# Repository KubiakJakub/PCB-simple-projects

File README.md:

# PCB simple projects
 Repo made for learning purpose only

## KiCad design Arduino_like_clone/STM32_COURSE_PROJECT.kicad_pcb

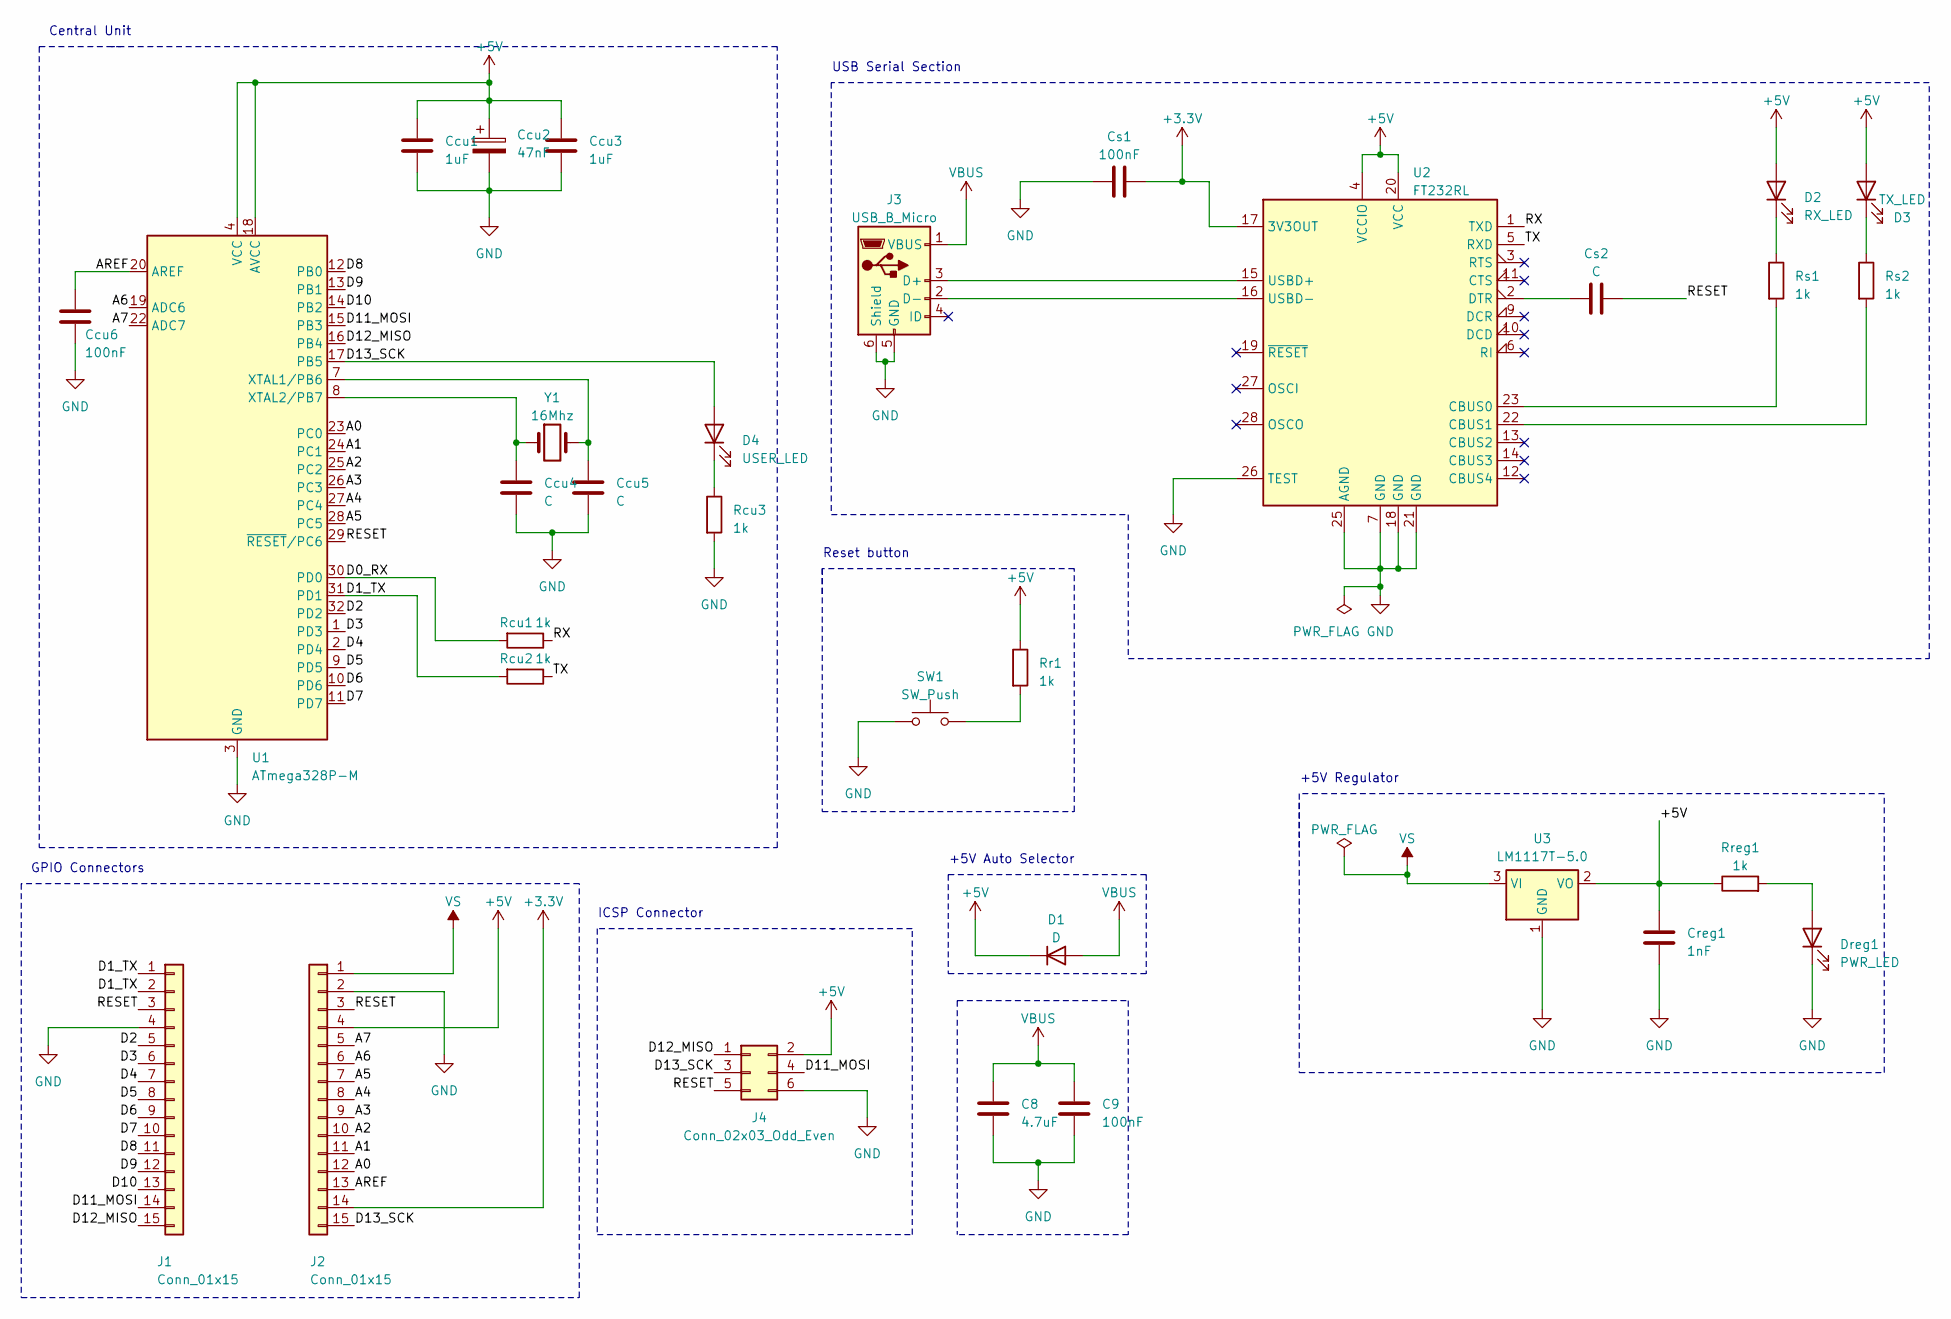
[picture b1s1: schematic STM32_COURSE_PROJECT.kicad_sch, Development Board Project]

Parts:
C8: 4.7uF; C_1206_3216Metric_Pad1.33x1.80mm_HandSolder
C9: 100nF; C_0805_2012Metric_Pad1.18x1.45mm_HandSolder
Ccu1, Ccu3: 1uF; C_0805_2012Metric_Pad1.18x1.45mm_HandSolder
Ccu2: 47nF; C_1206_3216Metric_Pad1.33x1.80mm_HandSolder
Ccu4, Ccu5: C; C_0805_2012Metric_Pad1.18x1.45mm_HandSolder
Ccu6: 100nF; C_0805_2012Metric_Pad1.18x1.45mm_HandSolder
Creg1: 1nF; C_0805_2012Metric_Pad1.18x1.45mm_HandSolder
Cs1: 100nF; C_0805_2012Metric_Pad1.18x1.45mm_HandSolder
Cs2: C; C_0805_2012Metric_Pad1.18x1.45mm_HandSolder
D1: D; D_SOD-123
D2: RX_LED; LED_0603_1608Metric_Pad1.05x0.95mm_HandSolder
D3: TX_LED; LED_0603_1608Metric_Pad1.05x0.95mm_HandSolder
D4: USER_LED; LED_0603_1608Metric_Pad1.05x0.95mm_HandSolder
Dreg1: PWR_LED; LED_0603_1608Metric_Pad1.05x0.95mm_HandSolder
J1, J2: Conn_01x15; PinHeader_1x15_P2.54mm_Vertical
J3: USB_B_Micro; USB_Mini-B_Lumberg_2486_01_Horizontal
J4: Conn_02x03_Odd_Even; PinHeader_2x03_P2.54mm_Vertical
Rcu1, Rcu2, Rcu3: 1k; R_0805_2012Metric_Pad1.20x1.40mm_HandSolder
Rr1: 1k; R_0805_2012Metric_Pad1.20x1.40mm_HandSolder
Rreg1: 1k; R_0805_2012Metric_Pad1.20x1.40mm_HandSolder
Rs1, Rs2: 1k; R_0805_2012Metric_Pad1.20x1.40mm_HandSolder
SW1: SW_Push; SW_Push_1P1T_NO_6x6mm_H9.5mm
U1: ATmega328P-M; QFN-32-1EP_5x5mm_P0.5mm_EP3.1x3.1mm
U2: FT232RL; SSOP-28_5.3x10.2mm_P0.65mm
U3: LM1117T-5.0; TO-220-3_Horizontal_TabDown
Y1: 16Mhz; Crystal_SMD_3225-4Pin_3.2x2.5mm_HandSoldering

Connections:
+3.3V: Cs1.2, J2.14, U2.17 (3V3OUT)
+5V: Ccu1.1, Ccu2.1, Ccu3.1, Creg1.1, D1.1 (K), D2.2 (A), D3.2 (A), J2.4, J4.2, Rr1.1, Rreg1.1, U1.4 (VCC), U1.6 (VCC), U1.18 (AVCC), U2.4 (VCCIO), U2.20 (VCC), U3.2 (VO)
/A0: J2.12, U1.23 (PC0)
/A1: J2.11, U1.24 (PC1)
/A2: J2.10, U1.25 (PC2)
/A3: J2.9, U1.26 (PC3)
/A4: J2.8, U1.27 (PC4)
/A5: J2.7, U1.28 (PC5)
/A6: J2.6, U1.19 (ADC6)
/A7: J2.5, U1.22 (ADC7)
/AREF: Ccu6.1, J2.13, U1.20 (AREF)
/D0_RX: Rcu1.2, U1.30 (PD0)
/D1_TX: J1.1, J1.2, Rcu2.2, U1.31 (PD1)
/D2: J1.5, U1.32 (PD2)
/D3: J1.6, U1.1 (PD3)
/D4: J1.7, U1.2 (PD4)
/D5: J1.8, U1.9 (PD5)
/D6: J1.9, U1.10 (PD6)
/D7: J1.10, U1.11 (PD7)
/D8: J1.11, U1.12 (PB0)
/D9: J1.12, U1.13 (PB1)
/D10: J1.13, U1.14 (PB2)
/D11_MOSI: J1.14, J4.4, U1.15 (PB3)
/D12_MISO: J1.15, J4.1, U1.16 (PB4)
/D13_SCK: D4.2 (A), J2.15, J4.3, U1.17 (PB5)
/RESET: Cs2.2, J1.3, J2.3, J4.5, U1.29 (~RESET/PC6)
/RX: Rcu1.1, U2.1 (TXD)
/TX: Rcu2.1, U2.5 (RXD)
GND: C8.2, C9.2, Ccu1.2, Ccu2.2, Ccu3.2, Ccu4.2, Ccu5.2, Ccu6.2, Creg1.2, Cs1.1, Dreg1.1 (K), J1.4, J2.2, J3.5 (GND), J3.6 (Shield), J4.6, Rcu3.2, SW1.1, U1.3 (GND), U1.5 (GND), U1.21 (GND), U1.33 (GND), U2.7 (GND), U2.18 (GND), U2.21 (GND), U2.25 (AGND), U2.26 (TEST), U3.1 (GND)
unnamed: D2.1 (K), Rs1.1
unnamed: D3.1 (K), Rs2.1
unnamed: D4.1 (K), Rcu3.1
unnamed: Dreg1.2 (A), Rreg1.2
unnamed: J3.3 (D+), U2.15 (USBD+)
unnamed: J3.2 (D-), U2.16 (USBD-)
unnamed: Rr1.2, SW1.2
unnamed: Ccu5.1, U1.7 (XTAL1/PB6), Y1.2
unnamed: Ccu4.1, U1.8 (XTAL2/PB7), Y1.1
unnamed: Rs1.2, U2.23 (CBUS0)
unnamed: Rs2.2, U2.22 (CBUS1)
unnamed: Cs2.1, U2.2 (DTR)
VBUS: C8.1, C9.1, D1.2 (A), J3.1 (VBUS)
VS: J2.1, U3.3 (VI)

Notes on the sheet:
+5V Auto Selector
GPIO Connectors
Central Unit
USB Serial Section
+5V Regulator
Reset button
ICSP Connector

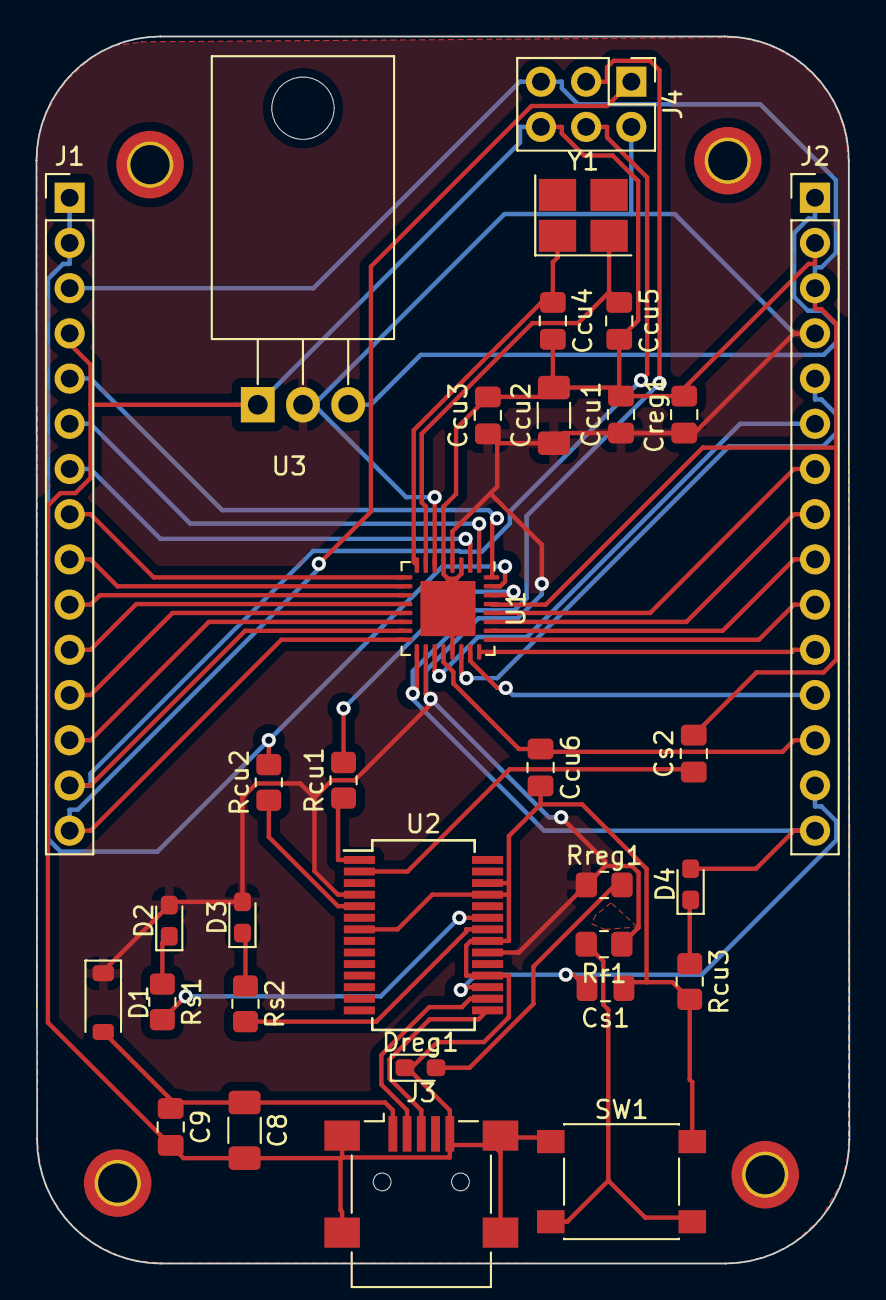
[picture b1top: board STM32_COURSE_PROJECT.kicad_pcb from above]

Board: 2 copper layers, 45.7 x 68.9 mm, 32 parts (0 on the bottom side), 43 nets.

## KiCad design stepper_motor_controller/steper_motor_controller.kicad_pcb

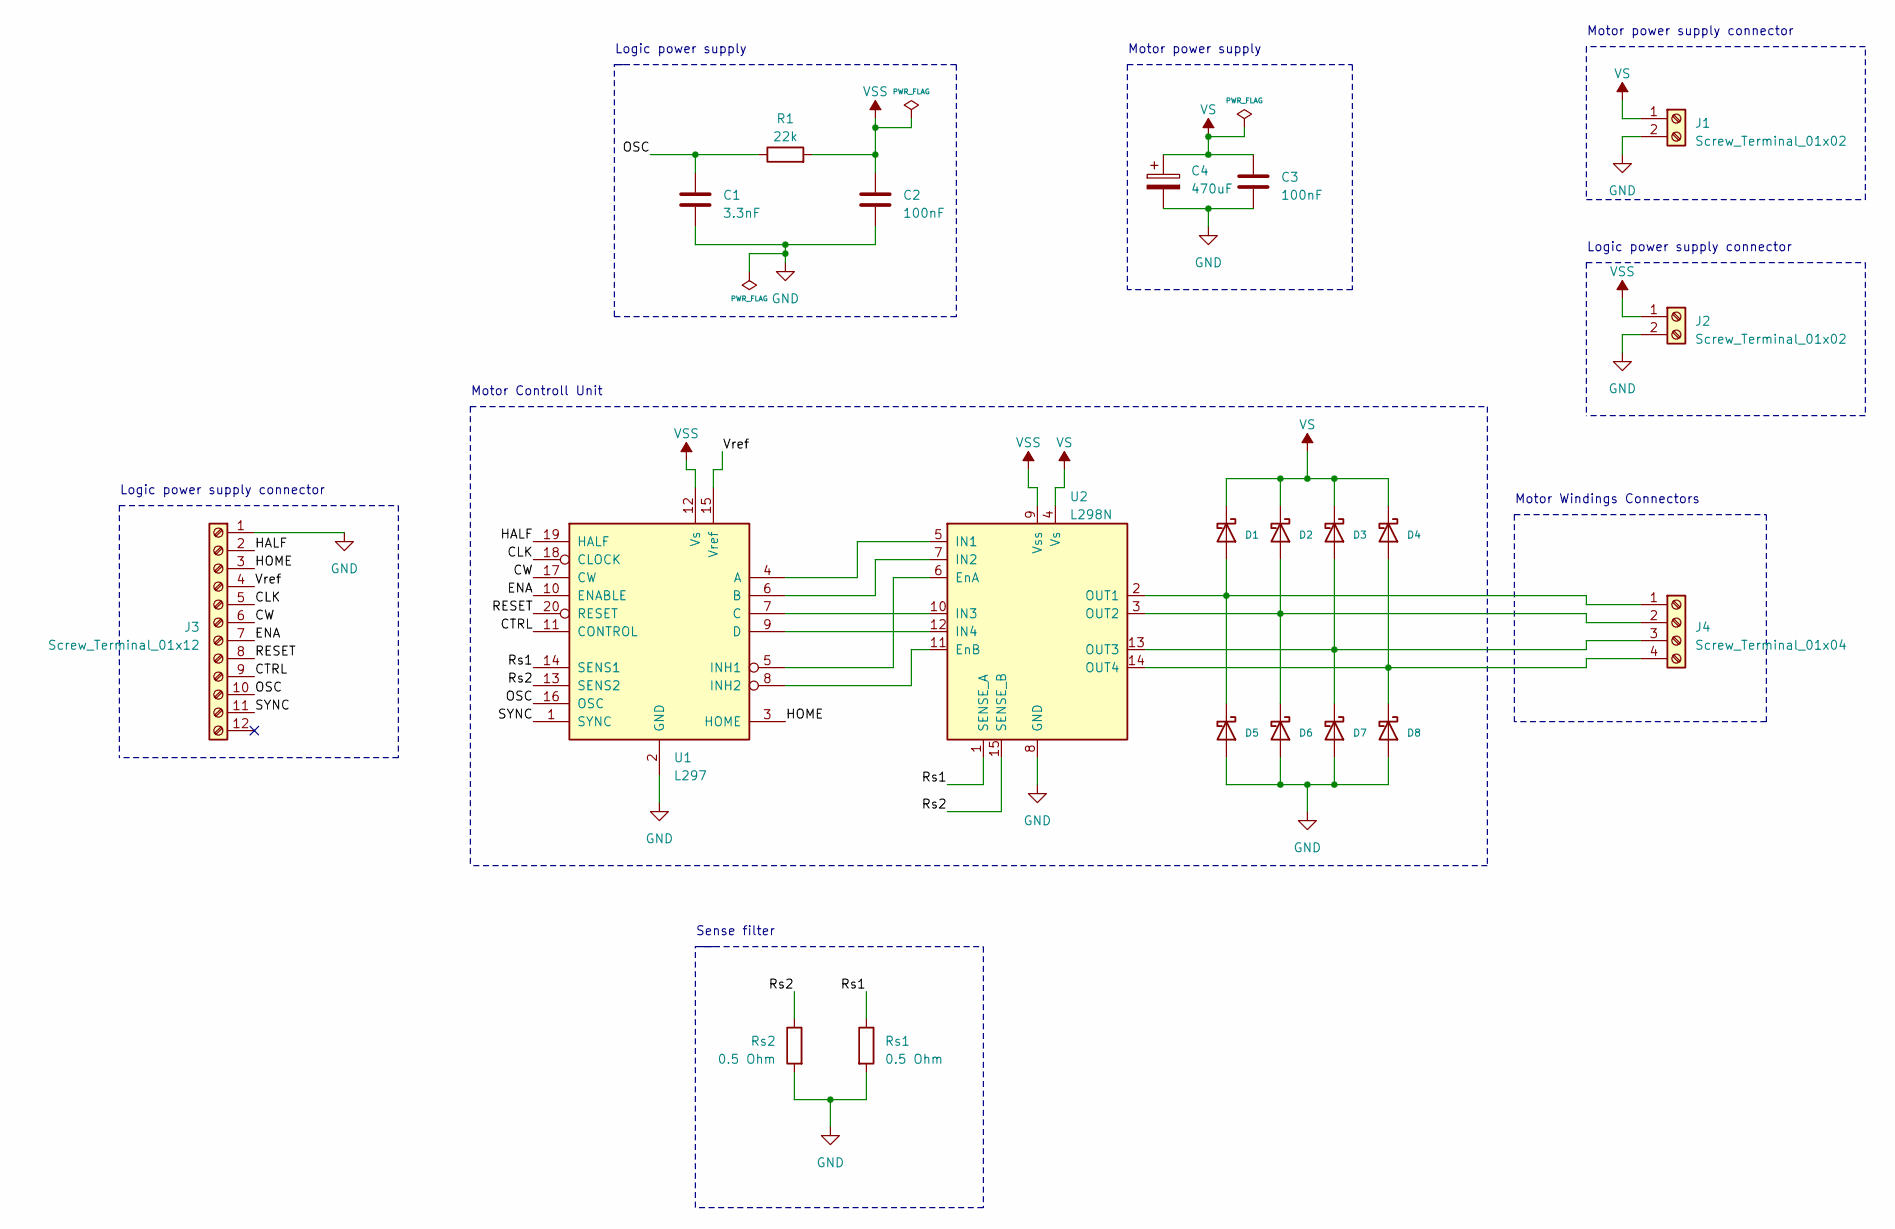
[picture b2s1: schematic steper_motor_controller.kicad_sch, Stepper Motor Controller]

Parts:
C1: 3.3nF; C_Rect_L10.0mm_W3.0mm_P7.50mm_FKS3_FKP3
C2, C3: 100nF; C_Rect_L7.5mm_W6.5mm_P5.00mm
C4: 470uF; CP_Radial_D13.0mm_P5.00mm
D1, D2, D3, D4, D5, D6, D7, D8: D_Schottky; D_DO-27_P15.24mm_Horizontal
J1, J2: Screw_Terminal_01x02; TerminalBlock_Phoenix_MKDS-1,5-2-5.08_1x02_P5.08mm_Horizont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
J3: Screw_Terminal_01x12; TerminalBlock_Phoenix_MKDS-3-12-5.08_1x12_P5.08mm_Horizontal
J4: Screw_Terminal_01x04; TerminalBlock_Phoenix_MKDS-1,5-4-5.08_1x04_P5.08mm_Horizont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
R1: 22k; R_Axial_DIN0922_L20.0mm_D9.0mm_P25.40mm_Horizontal
Rs1, Rs2: 0.5 Ohm; R_Axial_DIN0414_L11.9mm_D4.5mm_P15.24mm_Horizontal
U1: L297; DIP-20_W7.62mm
U2: L298N; TO-220-15_P2.54x2.54mm_StaggerOdd_Lead4.58mm_Vertical

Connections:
/CLK: J3.5, U1.18 (CLOCK)
/CTRL: J3.9, U1.11 (CONTROL)
/CW: J3.6, U1.17 (CW)
/ENA: J3.7, U1.10 (ENABLE)
/HALF: J3.2, U1.19 (HALF)
/HOME: J3.3, U1.3 (HOME)
/OSC: C1.1, J3.10, R1.1, U1.16 (OSC)
/RESET: J3.8, U1.20 (RESET)
/Rs1: Rs1.1, U1.14 (SENS1), U2.1 (SENSE_A)
/Rs2: Rs2.1, U1.13 (SENS2), U2.15 (SENSE_B)
/SYNC: J3.11, U1.1 (SYNC)
/Vref: J3.4, U1.15 (Vref)
GND: C1.2, C2.2, C3.2, C4.2, D5.2 (A), D6.2 (A), D7.2 (A), D8.2 (A), J1.2, J2.2, J3.1, Rs1.2, Rs2.2, U1.2 (GND), U2.8 (GND)
unnamed: D1.2 (A), D5.1 (K), J4.1, U2.2 (OUT1)
unnamed: D2.2 (A), D6.1 (K), J4.2, U2.3 (OUT2)
unnamed: D3.2 (A), D7.1 (K), J4.3, U2.13 (OUT3)
unnamed: D4.2 (A), D8.1 (K), J4.4, U2.14 (OUT4)
unnamed: U1.4 (A), U2.5 (IN1)
unnamed: U1.6 (B), U2.7 (IN2)
unnamed: U1.7 (C), U2.10 (IN3)
unnamed: U1.9 (D), U2.12 (IN4)
unnamed: U1.5 (INH1), U2.6 (EnA)
unnamed: U1.8 (INH2), U2.11 (EnB)
VS: C3.1, C4.1, D1.1 (K), D2.1 (K), D3.1 (K), D4.1 (K), J1.1, U2.4 (Vs)
VSS: C2.1, J2.1, R1.2, U1.12 (Vs), U2.9 (Vss)

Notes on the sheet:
Sense filter
Motor power supply connector
Motor power supply
Logic power supply
Logic power supply connector
Motor Windings Connectors
Motor Controll Unit

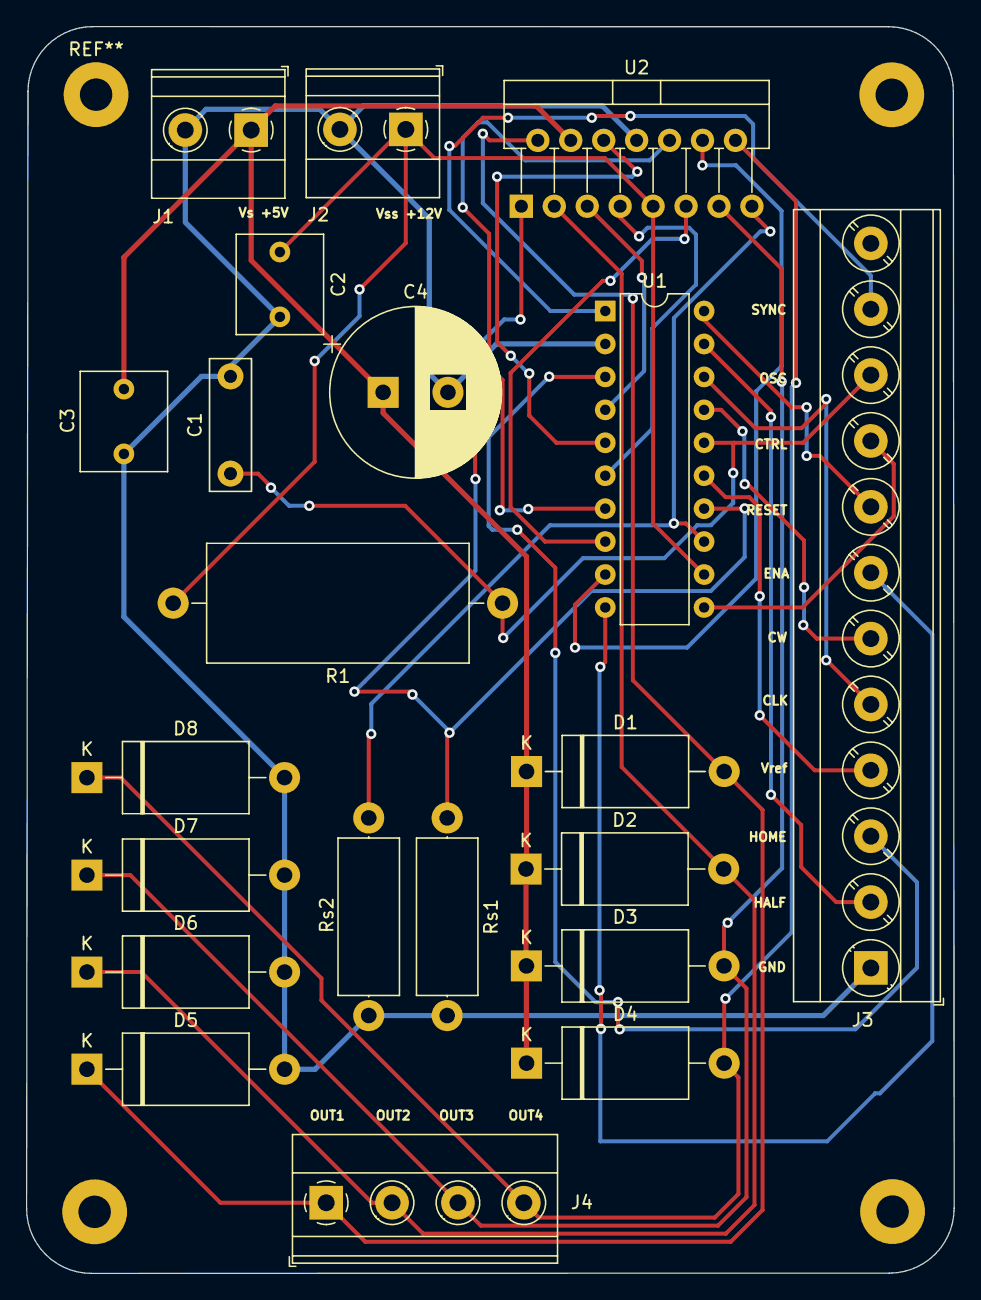
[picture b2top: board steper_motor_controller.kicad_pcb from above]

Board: 2 copper layers, 71.5 x 96.1 mm, 21 parts (0 on the bottom side), 25 nets.

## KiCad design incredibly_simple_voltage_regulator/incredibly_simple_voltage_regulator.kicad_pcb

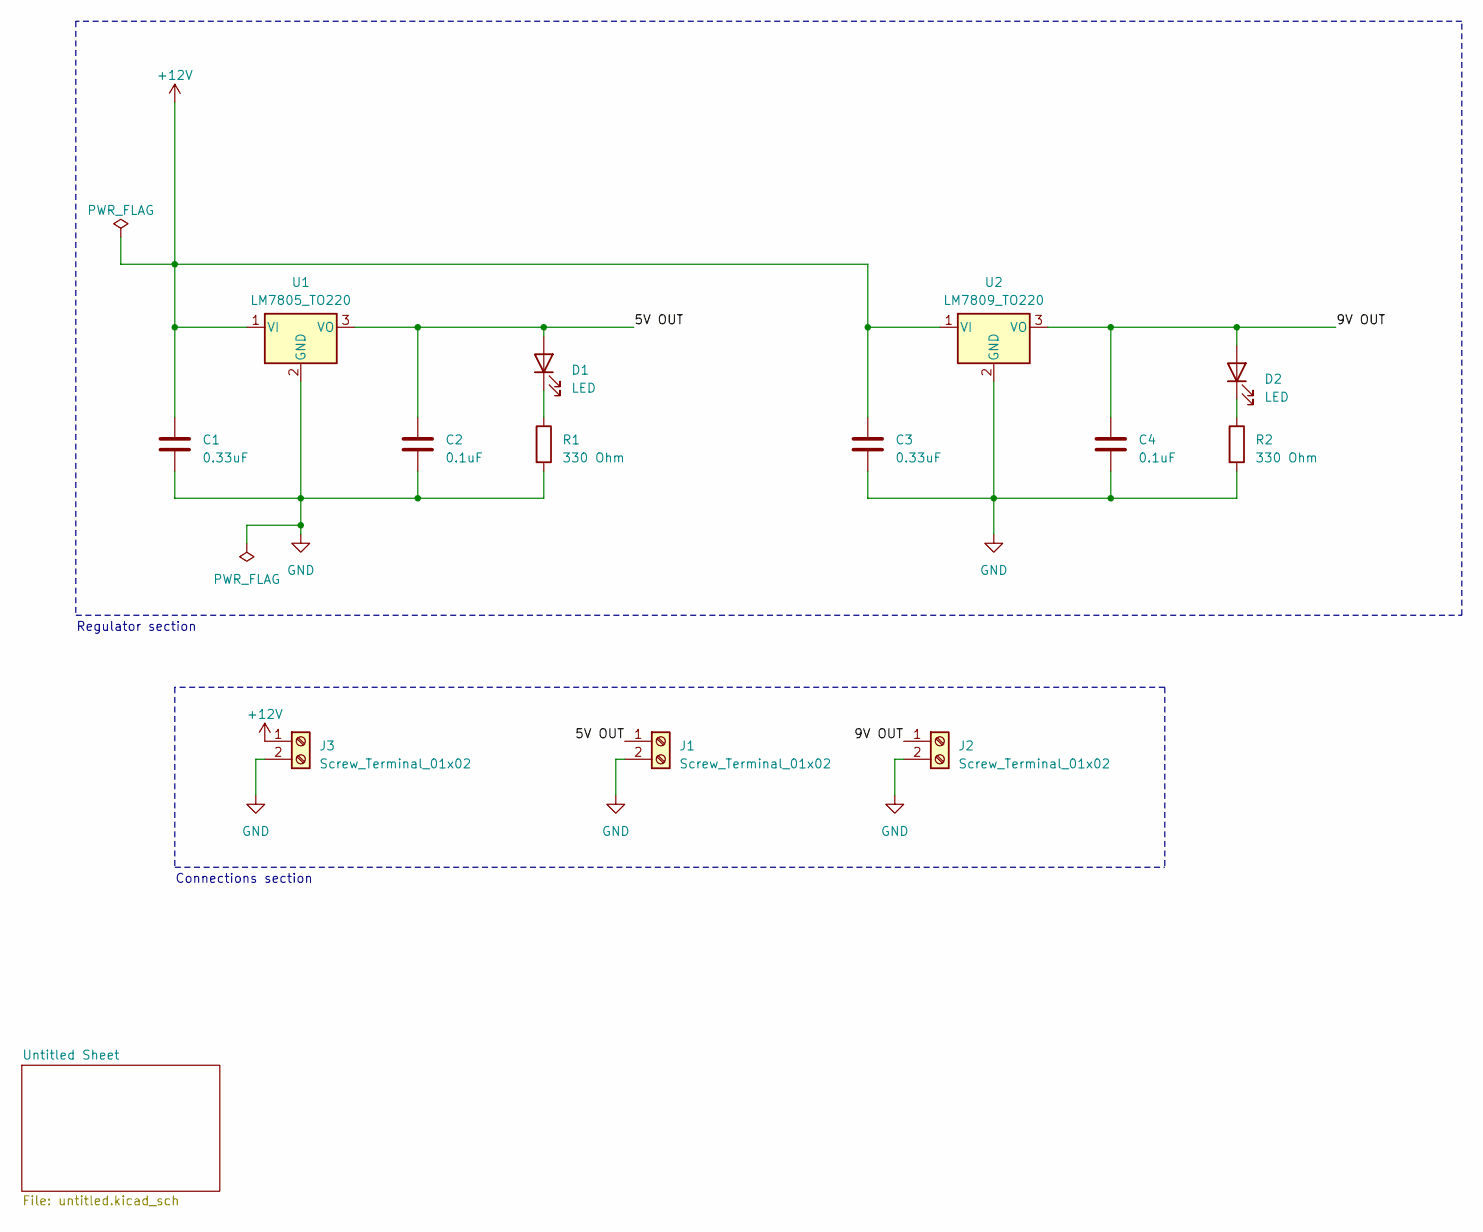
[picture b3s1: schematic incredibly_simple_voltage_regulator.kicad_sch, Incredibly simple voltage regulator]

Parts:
C1, C3: 0.33uF; C_Disc_D4.7mm_W2.5mm_P5.00mm
C2, C4: 0.1uF; C_Disc_D4.7mm_W2.5mm_P5.00mm
D1, D2: LED; LED_D4.0mm
J1, J2, J3: Screw_Terminal_01x02; TerminalBlock_Phoenix_MKDS-1,5-2_1x02_P5.00mm_Horizontal
R1, R2: 330 Ohm; R_Axial_DIN0207_L6.3mm_D2.5mm_P7.62mm_Horizontal
U1: LM7805_TO220; TO-220-3_Vertical
U2: LM7809_TO220; TO-220-3_Vertical

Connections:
+12V: C1.1, C3.1, J3.1, U1.1 (VI), U2.1 (VI)
/5V OUT: C2.1, D1.2 (A), J1.1, U1.3 (VO)
/9V OUT: C4.1, D2.2 (A), J2.1, U2.3 (VO)
GND: C1.2, C2.2, C3.2, C4.2, J1.2, J2.2, J3.2, R1.2, R2.2, U1.2 (GND), U2.2 (GND)
unnamed: D1.1 (K), R1.1
unnamed: D2.1 (K), R2.1

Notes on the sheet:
Connections section
Regulator section

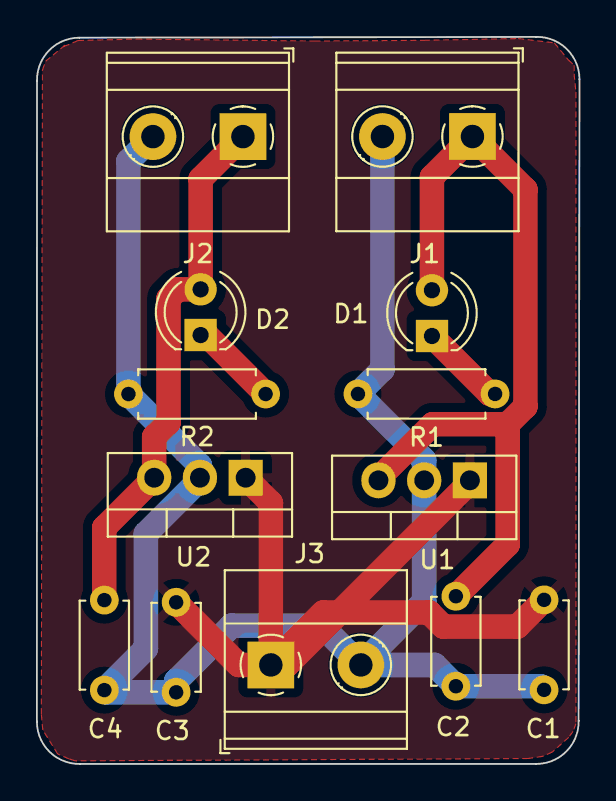
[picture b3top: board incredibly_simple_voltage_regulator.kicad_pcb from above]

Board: 6 copper layers, 30.1 x 40.4 mm, 13 parts (0 on the bottom side), 6 nets.

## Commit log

2023-05-08 Voltage regulator
2023-05-08 Stepper_motor_controler
2023-05-08 Arduino_clone
